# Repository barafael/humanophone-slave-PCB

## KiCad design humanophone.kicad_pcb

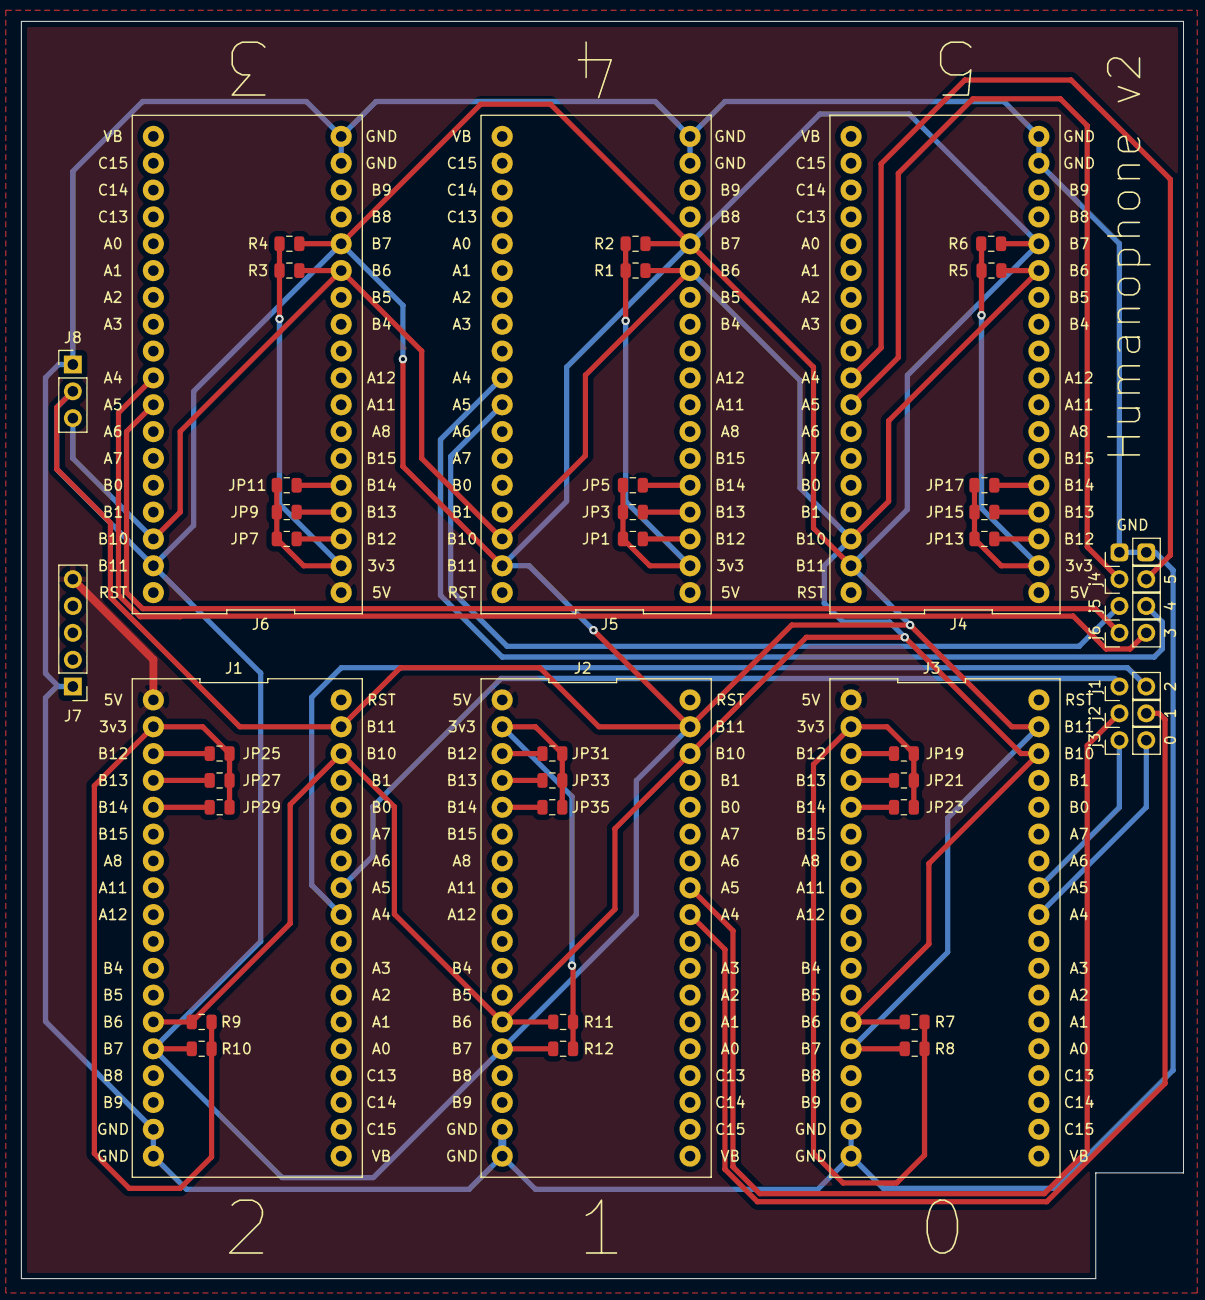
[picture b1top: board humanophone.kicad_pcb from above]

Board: 2 copper layers, 110.0 x 119.0 mm, 45 parts (0 on the bottom side), 40 nets.

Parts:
GND: Conn_01x02; PinHeader_1x02_P2.54mm_Vertical
J1, J2, J3, J4, J5, J6: longan-nano; LONGAN_NANO
J7: Conn_01x05; PinHeader_1x05_P2.54mm_Vertical
J8: Conn_01x03; PinHeader_1x03_P2.54mm_Vertical
JP1, JP3, JP5, JP7, JP9, JP11, JP13, JP15, JP17, JP19, JP21, JP23, JP25, JP27, JP29, JP31, JP33, JP35: Jumper; R_0805_2012Metric
R1, R2, R3, R4, R5, R6, R7, R8, R9, R10, R11, R12: R; R_0805_2012Metric
j1, j2, j3, j4, j5, j6: Conn_01x02; PinHeader_1x02_P2.54mm_Vertical

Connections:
5V: J1.1, J2.1, J3.1, J4.1, J5.1, J6.1, J7.5
/Sheet5E64FF21/DAC0: J1.28, j1.2
/Sheet5E64FF21/DAC1: J1.29, j1.1
/sheet5E64FF89/DAC0: J2.28, j2.2
/sheet5E64FF89/DAC1: J2.29, j2.1
/sheet5E64FFD2/DAC0: J3.28, j3.2
/sheet5E64FFD2/DAC1: J3.29, j3.1
/sheet5E64FFD4/DAC0: J4.28, j4.2
/sheet5E64FFD4/DAC1: J4.29, j4.1
/sheet5E650030/DAC0: J5.28, j5.2
/sheet5E650030/DAC1: J5.29, j5.1
/sheet5E650032/DAC0: J6.28, j6.2
/sheet5E650032/DAC1: J6.29, j6.1
GND: GND.1, GND.2, J1.17, J1.18, J2.17, J2.18, J3.17, J3.18, J4.17, J4.18, J5.17, J5.18, J6.17, J6.18, J7.1, J8.1
unnamed: J1.2, JP25.1, JP27.1, JP29.1, R9.1, R10.1
unnamed: J1.3, JP25.2
unnamed: J1.4, JP27.2
unnamed: J1.5, JP29.2
unnamed: J2.2, JP31.1, JP33.1, JP35.1, R11.1, R12.1
unnamed: J2.3, JP31.2
unnamed: J2.4, JP33.2
unnamed: J2.5, JP35.2
unnamed: J3.2, JP19.1, JP21.1, JP23.1, R7.1, R8.1
unnamed: J3.3, JP19.2
unnamed: J3.4, JP21.2
unnamed: J3.5, JP23.2
unnamed: J4.2, JP13.1, JP15.1, JP17.1, R5.1, R6.1
unnamed: J4.3, JP13.2
unnamed: J4.4, JP15.2
unnamed: J4.5, JP17.2
unnamed: J5.2, JP1.1, JP3.1, JP5.1, R1.1, R2.1
unnamed: J5.3, JP1.2
unnamed: J5.4, JP3.2
unnamed: J5.5, JP5.2
unnamed: J6.2, JP7.1, JP9.1, JP11.1, R3.1, R4.1
unnamed: J6.3, JP7.2
unnamed: J6.4, JP9.2
unnamed: J6.5, JP11.2
SCL0: J1.13, J1.34, J2.13, J2.34, J3.13, J3.34, J4.13, J4.34, J5.13, J5.34, J6.13, J6.34, J8.3, R1.2, R3.2, R5.2, R7.2, R9.2, R11.2
SDA0: J1.14, J1.35, J2.14, J2.35, J3.14, J3.35, J4.14, J4.35, J5.14, J5.35, J6.14, J6.35, J8.2, R2.2, R4.2, R6.2, R8.2, R10.2, R12.2

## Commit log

2020-04-05 add v2 of PCB
2020-04-05 add readme
2020-04-06 add v2 of schematic
